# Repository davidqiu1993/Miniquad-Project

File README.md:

#Miniquad(C) the Flight Robot Project
Miniquad(C) the Flight Robot Project is a research project on small quadcopter 
of the Robot Club, School of Software, Sun Yat-Sen University.

##Directory Structures
- `Development Environment` : The files or programs possibly necessary for 
    setting up the development environment.
    - `Drivers` : The drivers for devices used during the development 
        procedure.
    - `IDE` : The integrated development environment provided for the 
        development, such as the Arduino IDE.
    - `Miniquad Controller` : The controller to configurate or control the 
        Miniquad(C) robot.
- `Project Documents`: The documents of Miniquad(C) project, which provides 
    information about project schedule, development details, and so on.
    - `Protocals` : The common-committed protocals for communication, 
        controlling and other inter-machined activities.
- `Resources` : The resources and materials provided for better understanding 
    and development of the project or education for beginners.
    - `Sensors` : The documents and resources along with the sensors used 
        by the Miniquad(C) robot.
- `Source Code` : The source code of the project.
    - `Controller Software` : The source code of the controller software for 
        the Miniquad(C) robot. And the controller expected with different 
        editions on multiple platforms.
    - `Miniquad Circuit Design` : The Miniquad(C) robot circuit design 
        contents.
    - `Miniquad Software` : The programs that run on the Miniquad(C) robot.

##Project Members
- David Qiu (david@davidqiu.com / www.davidqiu.com)

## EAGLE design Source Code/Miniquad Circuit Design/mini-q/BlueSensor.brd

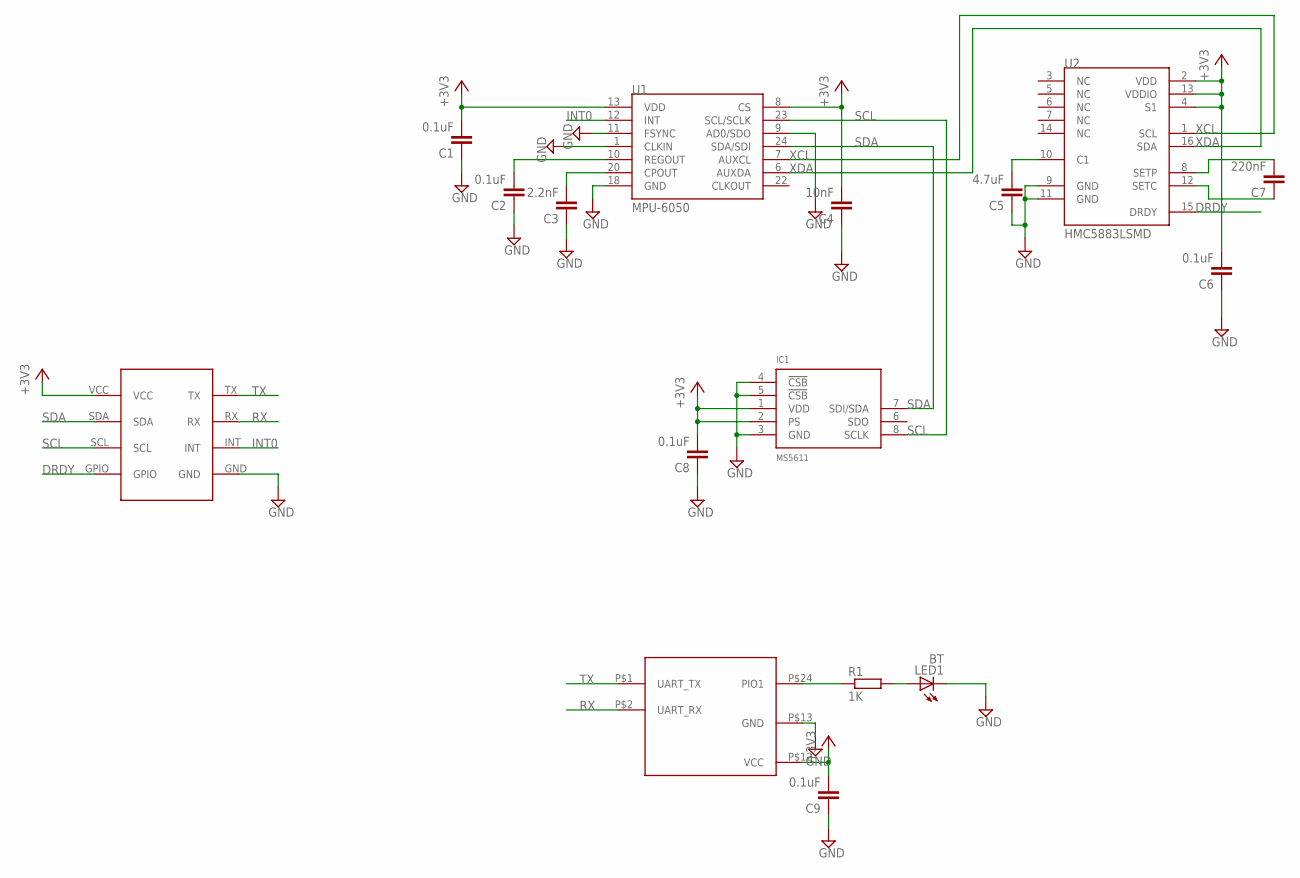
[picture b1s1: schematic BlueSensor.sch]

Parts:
C1, C2, C6, C8, C9: 0.1uF; C0805
C3: 2.2nF; C0805
C4: 10nF; C0805
C5: 4.7uF; C0805
C7: 220nF; C0805
IC1: MS5611; QFN-MS5611
LED1: BT; CHIPLED_0805
R1: 1K; R0805
U1: MPU-6050; QFN-24-TESTING
U2: HMC5883LSMD; 16LPCC
U$1: BLUESIMPLEHC-07; HC-07-SIMPLE
U$2: BLUESENSORBOARD; BLUESENSOR-BOARD

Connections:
+3V3: C1.2, C4.2, C6.2, C8.2, C9.2, IC1.1 (VDD), IC1.2 (PS), U1.8 (CS), U1.13 (VDD), U2.2 (VDD), U2.4 (S1), U2.13 (VDDIO), U$1.P$12 (VCC), U$2.VCC
DRDY: U2.15 (DRDY), U$2.GPIO
GND: C1.1, C2.1, C3.1, C4.1, C5.1, C6.1, C8.1, C9.1, IC1.3 (GND), IC1.4 (!CSB), IC1.5 (!CSB), LED1.C, U1.1 (CLKIN), U1.9 (AD0/SDO), U1.11 (FSYNC), U1.18 (GND), U2.9 (GND), U2.11 (GND), U$1.P$13 (GND), U$2.GND
INT0: U1.12 (INT), U$2.INT
unnamed: C5.2, U2.10 (C1)
unnamed: C7.2, U2.8 (SETP)
unnamed: C7.1, U2.12 (SETC)
unnamed: R1.1, U$1.P$24 (PIO1)
unnamed: LED1.A, R1.2
unnamed: C3.2, U1.20 (CPOUT)
unnamed: C2.2, U1.10 (REGOUT)
RX: U$1.P$2 (UART_RX), U$2.RX
SCL: IC1.8 (SCLK), U1.23 (SCL/SCLK), U$2.SCL
SDA: IC1.7 (SDI/SDA), U1.24 (SDA/SDI), U$2.SDA
TX: U$1.P$1 (UART_TX), U$2.TX
XCL: U1.7 (AUXCL), U2.1 (SCL)
XDA: U1.6 (AUXDA), U2.16 (SDA)

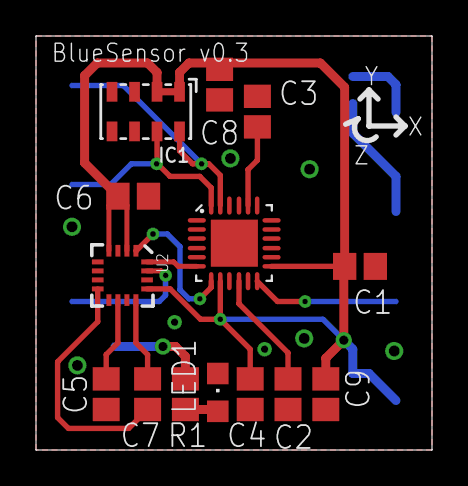
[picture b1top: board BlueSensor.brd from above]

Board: 2 copper layers, 22.0 x 23.0 mm, 16 parts (1 on the bottom side), 17 nets.

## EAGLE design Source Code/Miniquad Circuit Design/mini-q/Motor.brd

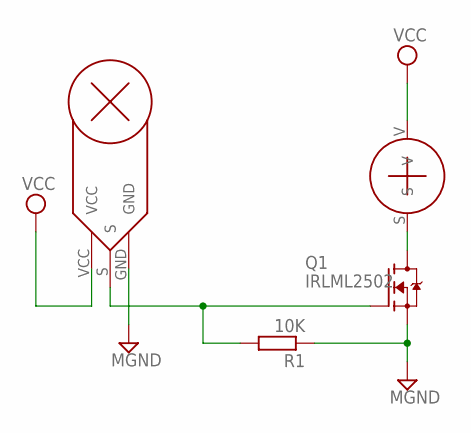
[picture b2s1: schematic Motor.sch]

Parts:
Q1: IRLML2502; SOT23-3
R1: 10K; R0805
U$1: MOTOR
U$2: MOTOR-BOARDBOARD; MOTOR-BOARD

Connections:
GND2: Q1.2 (S), R1.1, U$2.GND
unnamed: Q1.1 (G), R1.2, U$2.S
unnamed: Q1.3 (D), U$1.S
VCC: U$1.V, U$2.VCC

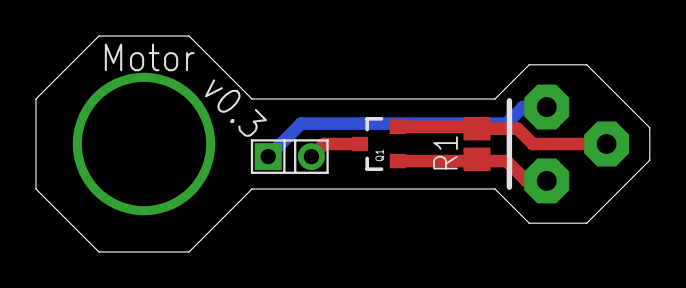
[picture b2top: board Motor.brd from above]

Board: 2 copper layers, 34.1 x 12.0 mm, 4 parts (1 on the bottom side), 4 nets.

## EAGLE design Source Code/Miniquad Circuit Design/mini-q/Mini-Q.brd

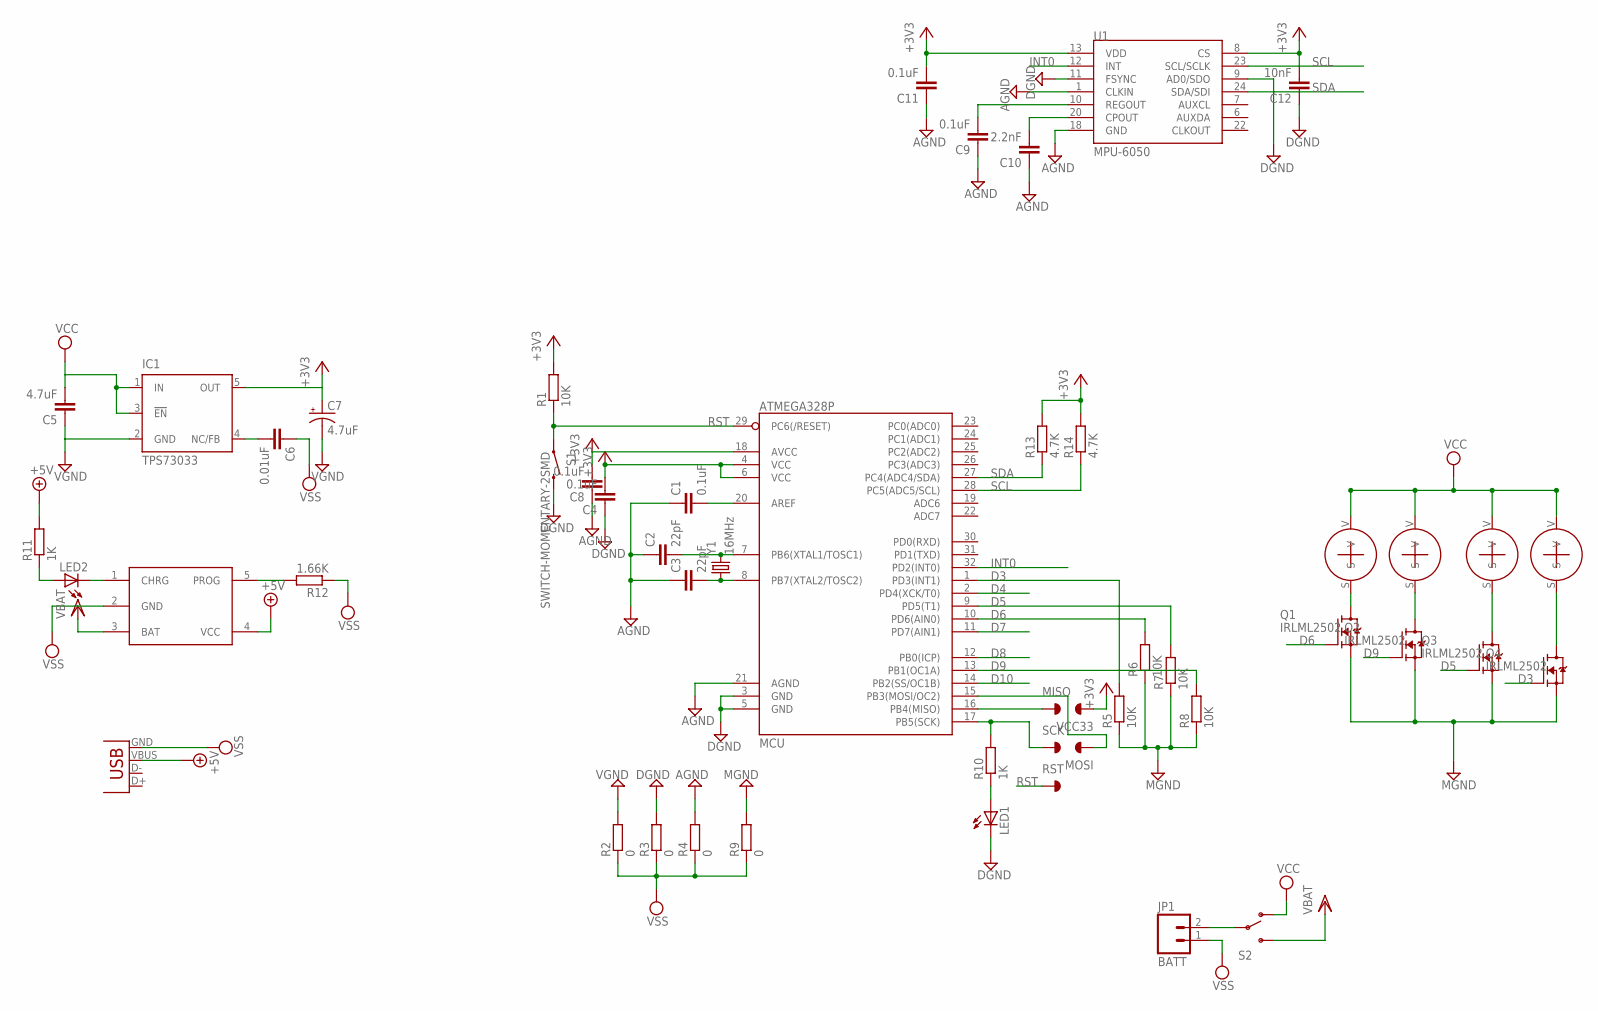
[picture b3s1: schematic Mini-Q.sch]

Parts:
C1, C4, C8, C9, C11: 0.1uF; C0805
C2, C3: 22pF; C0603
C5: 4.7uF; C0805
C6: 0.01uF; C0805
C7: 4.7uF; EIA3528
C10: 2.2nF; C0805
C12: 10nF; C0805
IC1: TPS73033; SOT23-DBV
JP1: BATT; 1X02
JP2: USBSMD; USB-MINIB
LED1, LED2: LEDSML0805; SML0805
MCU: ATMEGA328P; TQFP32-08
MISO: xx; POINT
MOSI: xx; POINT
Q1, Q2, Q3, Q4: IRLML2502; SOT23-3
R1, R5, R6, R7, R8: 10K; R0805
R2, R3, R4, R9: 0; R0805
R10, R11: 1K; R0805
R12: 1.66K; R0805
R13, R14: 4.7K; R0805
RST: xx; POINT
S1: SWITCH-MOMENTARY-2SMD; TACTILE_SWITCH_SMD
S2: SWITCH-SPDT-SMD-A; SWITCH-SPST-SMD-A
SCK: xx; POINT
U1: MPU-6050; QFN-24-TESTING
U$1, U$2, U$3, U$4: MOTOR
U$5: TP4055; SOT23-5
VCC33: xx; POINT
Y1: 16MHz; HC49US

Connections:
+3V3: C4.2, C7.A (+), C8.2, C11.2, C12.2, IC1.5 (OUT), MCU.4 (VCC), MCU.6 (VCC), MCU.18 (AVCC), R1.2, R13.2, R14.2, U1.8 (CS), U1.13 (VDD), VCC33.P$1
+5V: JP2.VBUS, R11.2, U$5.4 (VCC)
AGND: C1.1, C2.1, C3.1, C8.1, C9.1, C10.1, C11.1, MCU.21 (AGND), R4.2, U1.1 (CLKIN), U1.18 (GND)
D3: MCU.1 (PD3(INT1)), Q4.1 (G), R5.2
D4: MCU.2 (PD4(XCK/T0))
D5: MCU.9 (PD5(T1)), Q3.1 (G), R7.2
D6: MCU.10 (PD6(AIN0)), Q1.1 (G), R6.2
D7: MCU.11 (PD7(AIN1))
D8: MCU.12 (PB0(ICP))
D9: MCU.13 (PB1(OC1A)), Q2.1 (G), R8.2
D10: MCU.14 (PB2(SS/OC1B))
DGND: C4.1, C12.1, LED1.C, MCU.3 (GND), MCU.5 (GND), R3.2, S1.3 (2), U1.9 (AD0/SDO), U1.11 (FSYNC)
GND1: C5.1, C7.C (-), IC1.2 (GND), R2.2
GND2: Q1.2 (S), Q2.2 (S), Q3.2 (S), Q4.2 (S), R5.1, R6.1, R7.1, R8.1, R9.2
INT0: MCU.32 (PD2(INT0)), U1.12 (INT)
unnamed: C1.2, MCU.20 (AREF)
unnamed: MCU.16 (PB4(MISO)), MISO.P$1
unnamed: C3.2, MCU.8 (PB7(XTAL2/TOSC2)), Y1.1
unnamed: C2.2, MCU.7 (PB6(XTAL1/TOSC1)), Y1.2
unnamed: MCU.17 (PB5(SCK)), R10.2, SCK.P$1
unnamed: C6.2, IC1.4 (NC/FB)
unnamed: JP1.2, S2.2
unnamed: MCU.15 (PB3(MOSI/OC2)), MOSI.P$1
unnamed: Q1.3 (D), U$1.S
unnamed: Q2.3 (D), U$2.S
unnamed: Q3.3 (D), U$3.S
unnamed: Q4.3 (D), U$4.S
unnamed: LED1.A, R10.1
unnamed: C10.2, U1.20 (CPOUT)
unnamed: C9.2, U1.10 (REGOUT)
unnamed: LED2.A, R11.1
unnamed: LED2.C, U$5.1 (CHRG)
unnamed: R12.2, U$5.5 (PROG)
RST: MCU.29 (PC6(/RESET)), R1.1, RST.P$1, S1.1
SCL: MCU.28 (PC5(ADC5/SCL)), R14.1, U1.23 (SCL/SCLK)
SDA: MCU.27 (PC4(ADC4/SDA)), R13.1, U1.24 (SDA/SDI)
VCC: C5.2, IC1.1 (IN), IC1.3 (!EN), S2.1 (O), U$1.V, U$2.V, U$3.V, U$4.V
VDD: S2.3 (S), U$5.3 (BAT)
VSS: C6.1, JP1.1, JP2.GND, R2.1, R3.1, R4.1, R9.1, R12.1, U$5.2 (GND)

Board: 2 copper layers, 50 parts (8 on the bottom side), 35 nets, no tracks yet.

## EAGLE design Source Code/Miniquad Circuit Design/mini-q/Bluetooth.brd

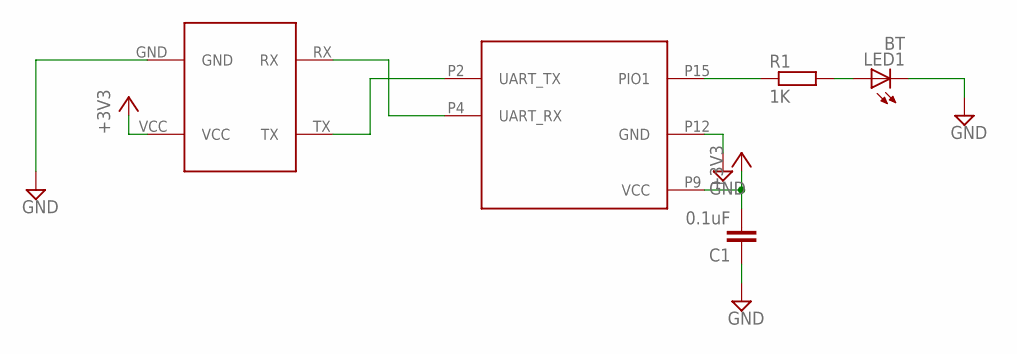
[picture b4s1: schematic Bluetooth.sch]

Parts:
C1: 0.1uF; C0805
LED1: BT; CHIPLED_0805
R1: 1K; R0805
U$1: BLUESIMPLE
U$2: BLUE-BOARD

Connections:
+3V3: C1.2, U$1.P9 (VCC), U$2.VCC
GND: C1.1, LED1.C, U$1.P12 (GND), U$2.GND
unnamed: U$1.P4 (UART_RX), U$2.RX
unnamed: U$1.P2 (UART_TX), U$2.TX
unnamed: R1.1, U$1.P15 (PIO1)
unnamed: LED1.A, R1.2

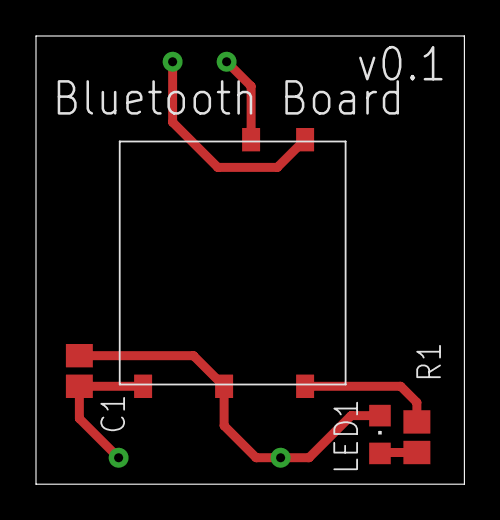
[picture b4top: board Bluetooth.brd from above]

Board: 2 copper layers, 23.8 x 24.9 mm, 5 parts (0 on the bottom side), 6 nets.

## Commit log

2014-03-02 Upload the existing project files.

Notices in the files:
parts and their libraries:
SparkFun-Sensors: Licensing: CC v3.0 Share-Alike You are welcome to use this library for commercial purposes.
xmaker: Licensing: CC v3.0 Attribution-Share Alike
http://creativecommons.org/licenses/by-sa/3.0
